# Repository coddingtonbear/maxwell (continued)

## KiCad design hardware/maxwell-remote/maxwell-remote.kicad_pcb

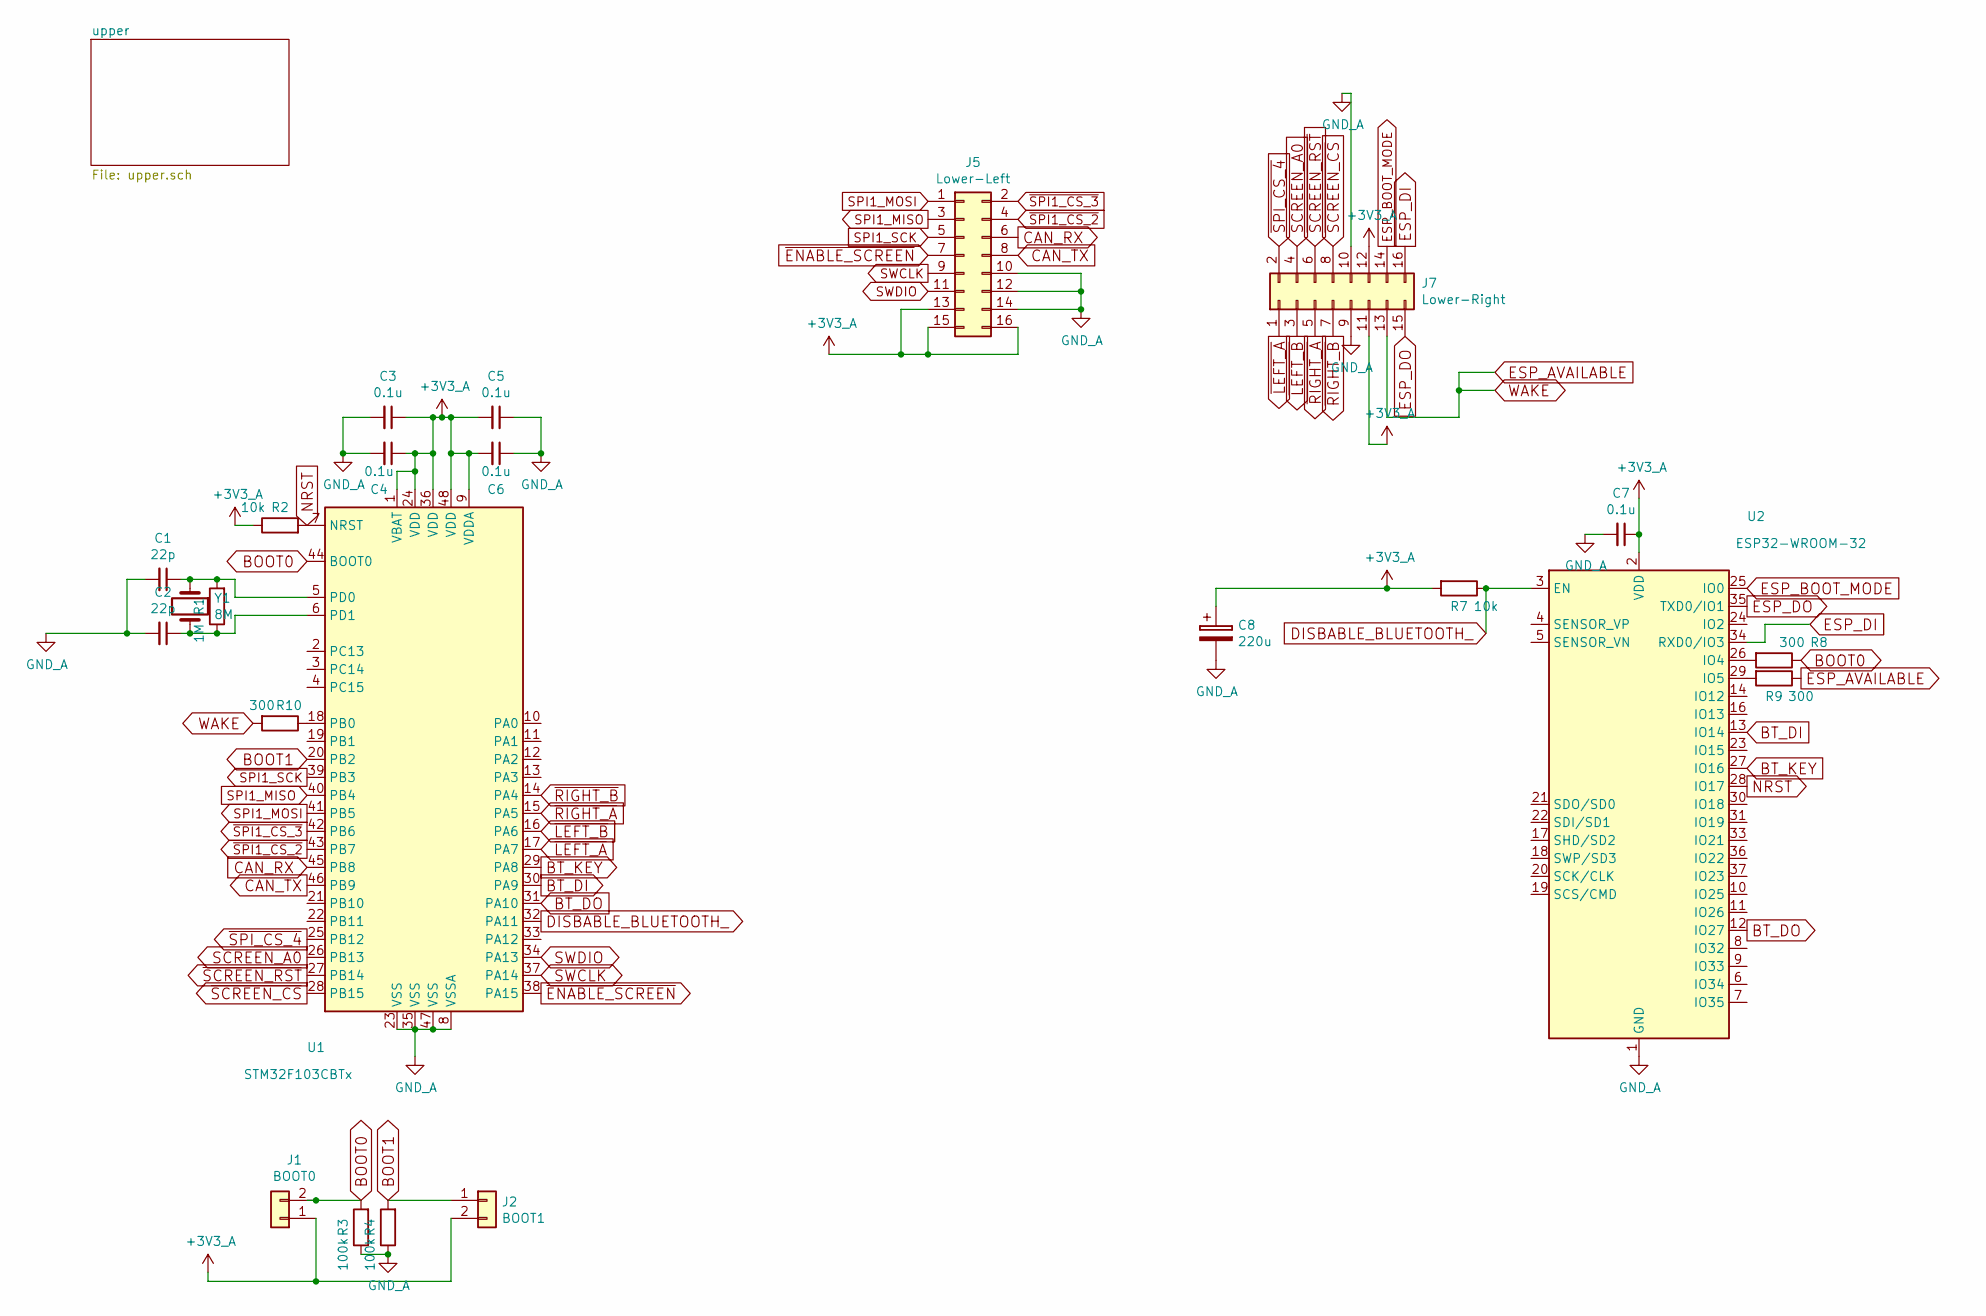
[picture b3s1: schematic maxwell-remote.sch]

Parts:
C1, C2: 22p; 0805_Milling
C3, C4, C5, C6, C7: 0.1u; 0805_Milling
C8: 220u; CP_Tantalum_Case-C_EIA-6032-28_Milling
J1: BOOT0; Pin_Header_Straight_1x02_Pitch1.27mm_JMP
J2: BOOT1; Pin_Header_Straight_1x02_Pitch1.27mm_JMP
J5: Lower-Left; PinHeader_2x08_P2.54mm_Vertical_LargePads
J7: Lower-Right; PinHeader_2x08_P2.54mm_Vertical_LargePads
R1: 1M; 0805_Milling
R2, R7: 10k; 0805_Milling
R3, R4: 100k; 0805_Milling
R8, R9, R10: 300; 0805_Milling
U1: STM32F103CBTx; QFP48-1.27MM-CASTELLATED
U2: ESP32-WROOM-32
Y1: 8M; Abracon-ABM2_LargePads

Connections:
+3V3_A: C3.1, C4.1, C5.2, C6.2, C7.1, C8.1, J1.1, J2.2, J5.13, J5.15, J5.16, J7.11, J7.12, R2.1, R7.2, U1.1 (VBAT), U1.9 (VDDA), U1.24 (VDD), U1.36 (VDD), U1.48 (VDD), U2.2 (VDD)
BOOT0: J1.2, R3.2, R8.1, U1.44 (BOOT0)
BOOT1: J2.1, R4.2, U1.20 (PB2)
BT_DI: U1.30 (PA9), U2.13 (IO14)
BT_DO: U1.31 (PA10), U2.12 (IO27)
BT_KEY: U1.29 (PA8), U2.27 (IO16)
CAN_RX: J5.6, U1.45 (PB8)
CAN_TX: J5.8, U1.46 (PB9)
DISBABLE_BLUETOOTH_: R7.1, U1.32 (PA11), U2.3 (EN)
ESP_AVAILABLE: J7.13, R9.1, R10.2
ESP_BOOT_MODE: J7.14, U2.25 (IO0)
ESP_DI: J7.16, U2.34 (RXD0/IO3)
ESP_DO: J7.15, U2.35 (TXD0/IO1)
GND_A: C1.2, C2.2, C3.2, C4.2, C5.1, C6.1, C7.2, C8.2, J5.10, J5.12, J5.14, J7.9, J7.10, R3.1, R4.1, U1.8 (VSSA), U1.23 (VSS), U1.35 (VSS), U1.47 (VSS), U2.1 (GND), U2.15 (GND), U2.38 (GND)
NRST: R2.2, U1.7 (NRST), U2.28 (IO17)
unnamed: C1.1, R1.2, U1.5 (PD0), Y1.1
unnamed: C2.1, R1.1, U1.6 (PD1), Y1.2
unnamed: R8.2, U2.26 (IO4)
unnamed: R9.2, U2.29 (IO5)
unnamed: R10.1, U1.18 (PB0)
SCREEN_A0: J7.4, U1.26 (PB13)
SPI1_MISO: J5.3, U1.40 (PB4)
SPI1_MOSI: J5.1, U1.41 (PB5)
SPI1_SCK: J5.5, U1.39 (PB3)
SWCLK: J5.9, U1.37 (PA14)
SWDIO: J5.11, U1.34 (PA13)
~ENABLE_SCREEN: J5.7, U1.38 (PA15)
~LEFT_A: J7.1, U1.17 (PA7)
~LEFT_B: J7.3, U1.16 (PA6)
~RIGHT_A: J7.5, U1.15 (PA5)
~RIGHT_B: J7.7, U1.14 (PA4)
~SCREEN_CS: J7.8, U1.28 (PB15)
~SCREEN_RST: J7.6, U1.27 (PB14)
~SPI1_CS_2: J5.4, U1.43 (PB7)
~SPI1_CS_3: J5.2, U1.42 (PB6)
~SPI_CS_4: J7.2, U1.25 (PB12)

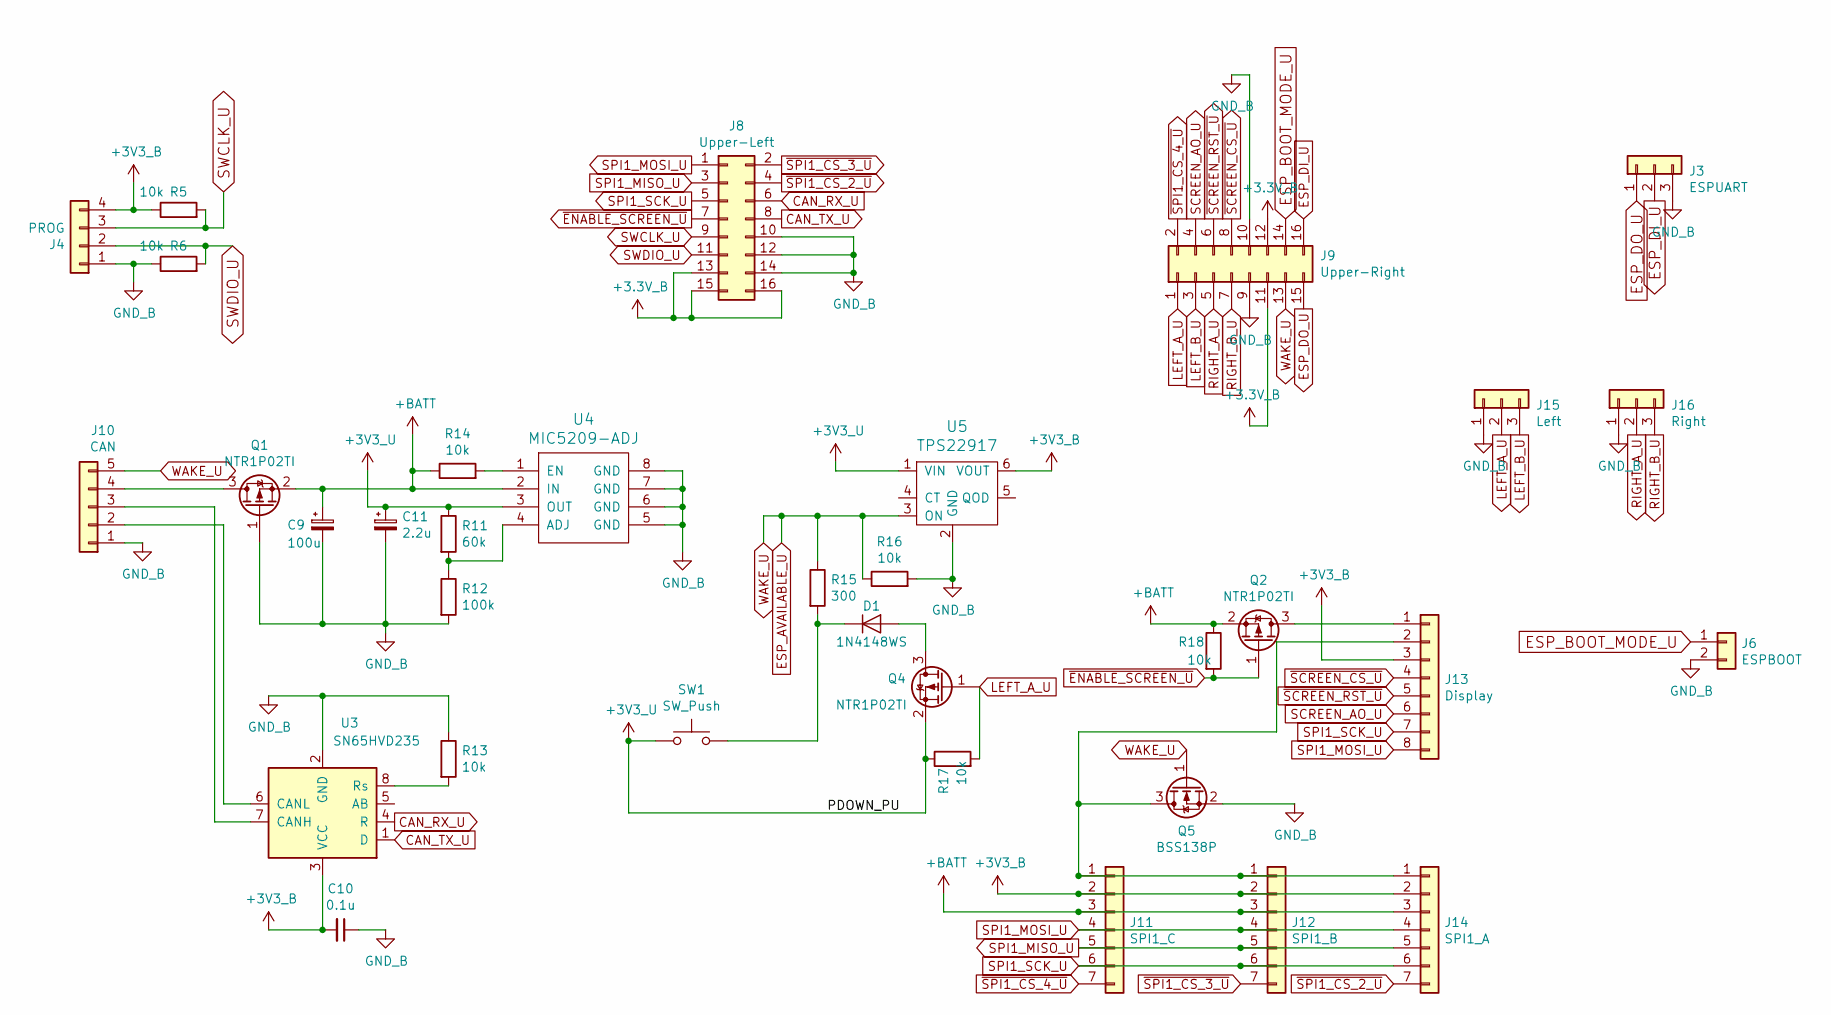
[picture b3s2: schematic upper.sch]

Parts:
C9: 100u; CP_Tantalum_Case-C_EIA-6032-28_Milling
C10: 0.1u; 0805_Milling
C11: 2.2u; CP_Tantalum_Case-C_EIA-6032-28_Milling
D1: 1N4148WS; D_SOD-323_HandSoldering
J3: ESPUART; JST_XH_B03B-XH-A_03x2.50mm_Straight_LargePads
J4: PROG; Pin_Header_Straight_1x04_Pitch2.54mm_LargePads
J6: ESPBOOT; Pin_Header_Straight_1x02_Pitch1.27mm_JMP
J8: Upper-Left; PinHeader_2x08_P2.54mm_Vertical_LargePads
J9: Upper-Right; PinHeader_2x08_P2.54mm_Vertical_LargePads
J10: CAN; JST_XH_B05B-XH-A_05x2.50mm_Straight_LargePads
J11: SPI1_C; JST_XH_B07B-XH-A_07x2.50mm_Straight_LargePads
J12: SPI1_B; JST_XH_B07B-XH-A_07x2.50mm_Straight_LargePads
J13: Display; JST_XH_B08B-XH-A_08x2.50mm_Straight_LargePads
J14: SPI1_A; JST_XH_B07B-XH-A_07x2.50mm_Straight_LargePads
J15: Left; JST_XH_B03B-XH-A_03x2.50mm_Straight_LargePads
J16: Right; JST_XH_B03B-XH-A_03x2.50mm_Straight_LargePads
Q1, Q2, Q4: NTR1P02TI; SOT-23_LargePads
Q5: BSS138P; SOT-23_LargePads
R5, R6, R13, R14, R16, R17, R18: 10k; 0805_Milling
R11: 60k; 0805_Milling
R12: 100k; 0805_Milling
R15: 300; 0805_Milling
SW1: SW_Push; SMD_MINI_BLACK_TACTILE_SWITCH
U3: SN65HVD235; SOIC-8_3.9x4.9mm_P1.27mm
U4: MIC5209-ADJ; SOIC-8_3.9x4.9mm_P1.27mm_LargePads
U5: TPS22917; SOT-23-6_Handsoldering

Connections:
+3V3_U: C11.1, Q4.2 (S), R11.1, R17.1, SW1.1, U4.3 (OUT), U5.1 (VIN)
+BATT: C9.1, J11.3, J12.3, J14.3, Q1.2 (S), Q2.2 (S), R14.1, R18.1, U4.2 (IN)
CAN_RX_U: J8.6, U3.4 (R)
CAN_TX_U: J8.8, U3.1 (D)
ESP_AVAILABLE_U: J9.13, J10.5, Q5.1 (G), R15.1, R16.1, U5.3 (ON)
ESP_BOOT_MODE_U: J6.1, J9.14
ESP_DI_U: J3.2, J9.16
ESP_DO_U: J3.1, J9.15
GND_B: C9.2, C10.1, C11.2, J3.3, J4.1, J6.2, J8.10, J8.12, J8.14, J9.9, J9.10, J10.1, J15.1, J16.1, Q1.1 (G), Q5.2 (S), R6.1, R12.2, R13.1, R16.2, U3.2 (GND), U4.5 (GND), U4.6 (GND), U4.7 (GND), U4.8 (GND), U5.2 (GND)
LEFT_A_U: J9.1, J15.2, Q4.1 (G), R17.2
LEFT_B_U: J9.3, J15.3
unnamed: D1.1 (K), R15.2, SW1.2
unnamed: D1.2 (A), Q4.3 (D)
unnamed: J10.2, U3.6 (CANL)
unnamed: J10.3, U3.7 (CANH)
unnamed: J10.4, Q1.3 (D)
unnamed: J11.1, J12.1, J13.2, J14.1, Q5.3 (D)
unnamed: J13.1, Q2.3 (D)
unnamed: R11.2, R12.1, U4.4 (ADJ)
unnamed: R13.2, U3.8 (Rs)
unnamed: R14.2, U4.1 (EN)
RIGHT_A_U: J9.5, J16.2
RIGHT_B_U: J9.7, J16.3
SCREEN_AO_U: J9.4, J13.6
SPI1_MISO_U: J8.3, J11.5, J12.5, J14.5
SPI1_MOSI_U: J8.1, J11.4, J12.4, J13.8, J14.4
SPI1_SCK_U: J8.5, J11.6, J12.6, J13.7, J14.6
SWCLK_U: J4.3, J8.9, R5.2
SWDIO_U: J4.2, J8.11, R6.2
~ENABLE_SCREEN_U: J8.7, Q2.1 (G), R18.2
~SCREEN_CS_U: J9.8, J13.4
~SCREEN_RST_U: J9.6, J13.5
~SPI1_CS_2_U: J8.4, J14.7
~SPI1_CS_3_U: J8.2, J12.7
~SPI1_CS_4_U: J9.2, J11.7

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
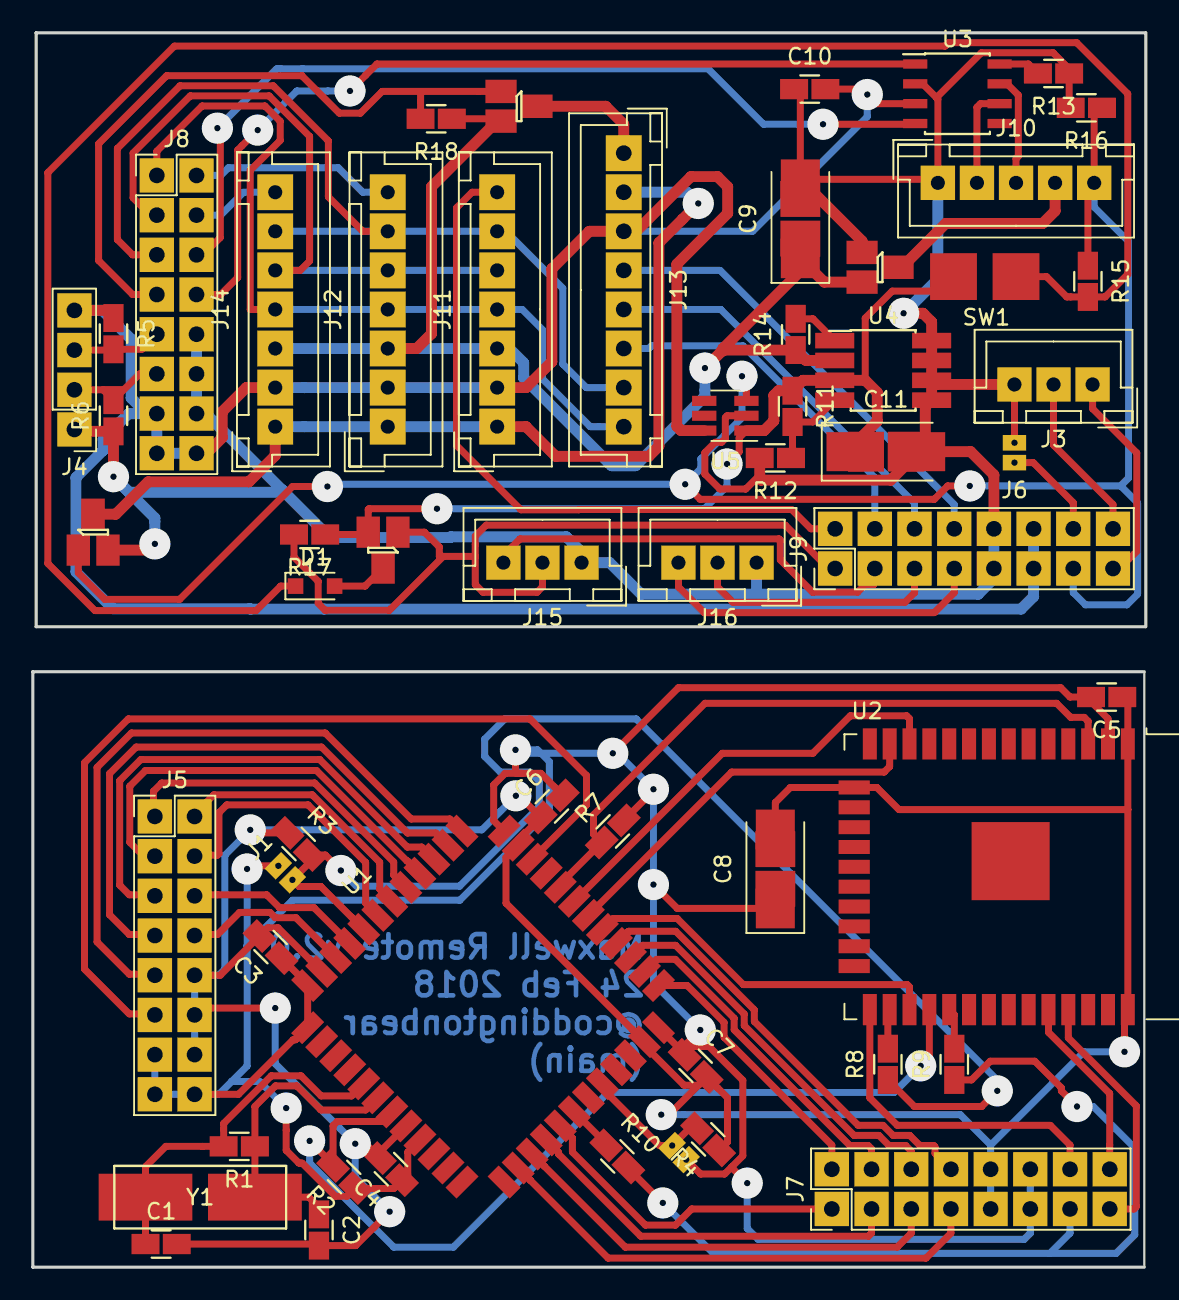
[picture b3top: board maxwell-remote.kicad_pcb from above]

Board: 2 copper layers, 71.2 x 79.0 mm, 57 parts (1 on the bottom side), 72 nets.

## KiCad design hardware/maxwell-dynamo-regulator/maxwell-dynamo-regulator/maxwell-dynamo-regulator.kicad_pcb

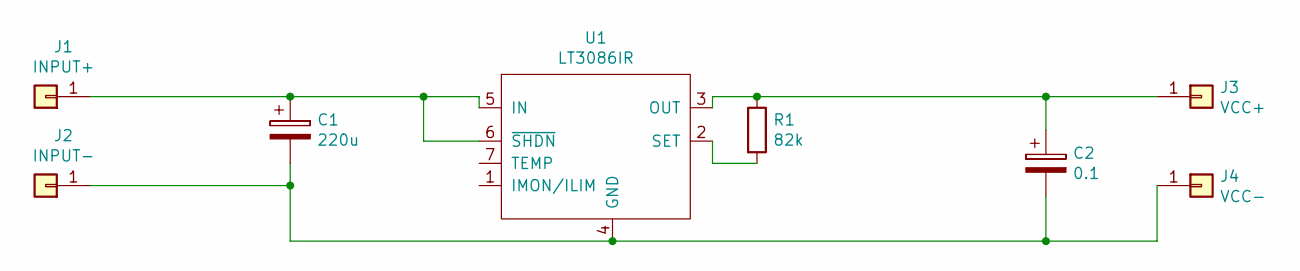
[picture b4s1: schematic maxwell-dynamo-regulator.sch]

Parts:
C1: 220u; C_Elec_8x10.2
C2: 0.1; JST_XH_B02B-XH-A_02x2.50mm_Straight_LargePads
J1: INPUT+; PinHeader_1x01_P2.54mm_Vertical
J2: INPUT-; PinHeader_1x01_P2.54mm_Vertical
J3: VCC+; PinHeader_1x01_P2.54mm_Vertical
J4: VCC-; PinHeader_1x01_P2.54mm_Vertical
R1: 82k; 0805_Milling
U1: LT3086IR; TO-263-7_TabPin4

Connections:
unnamed: C1.1, J1.1, U1.5 (IN), U1.6 (~SHDN)
unnamed: C1.2, C2.2, J2.1, J4.1, U1.4 (GND)
unnamed: C2.1, J3.1, R1.1, U1.3 (OUT)
unnamed: R1.2, U1.2 (SET)

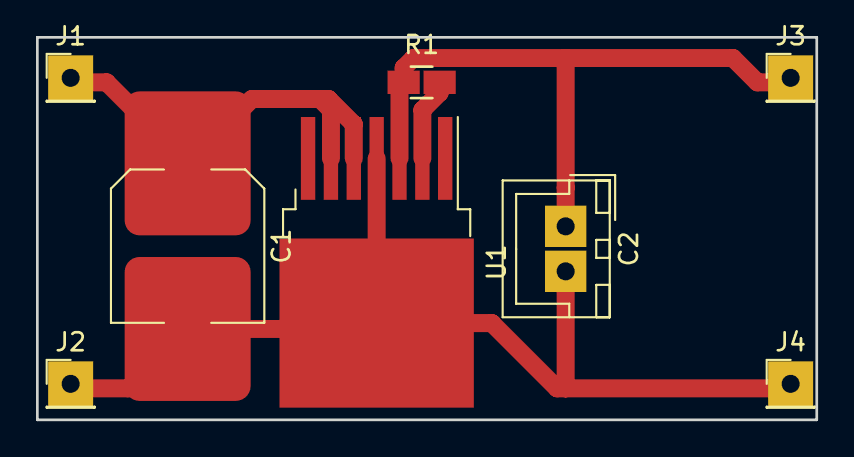
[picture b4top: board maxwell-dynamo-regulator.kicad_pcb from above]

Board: 2 copper layers, 43.3 x 21.2 mm, 8 parts (0 on the bottom side), 4 nets.

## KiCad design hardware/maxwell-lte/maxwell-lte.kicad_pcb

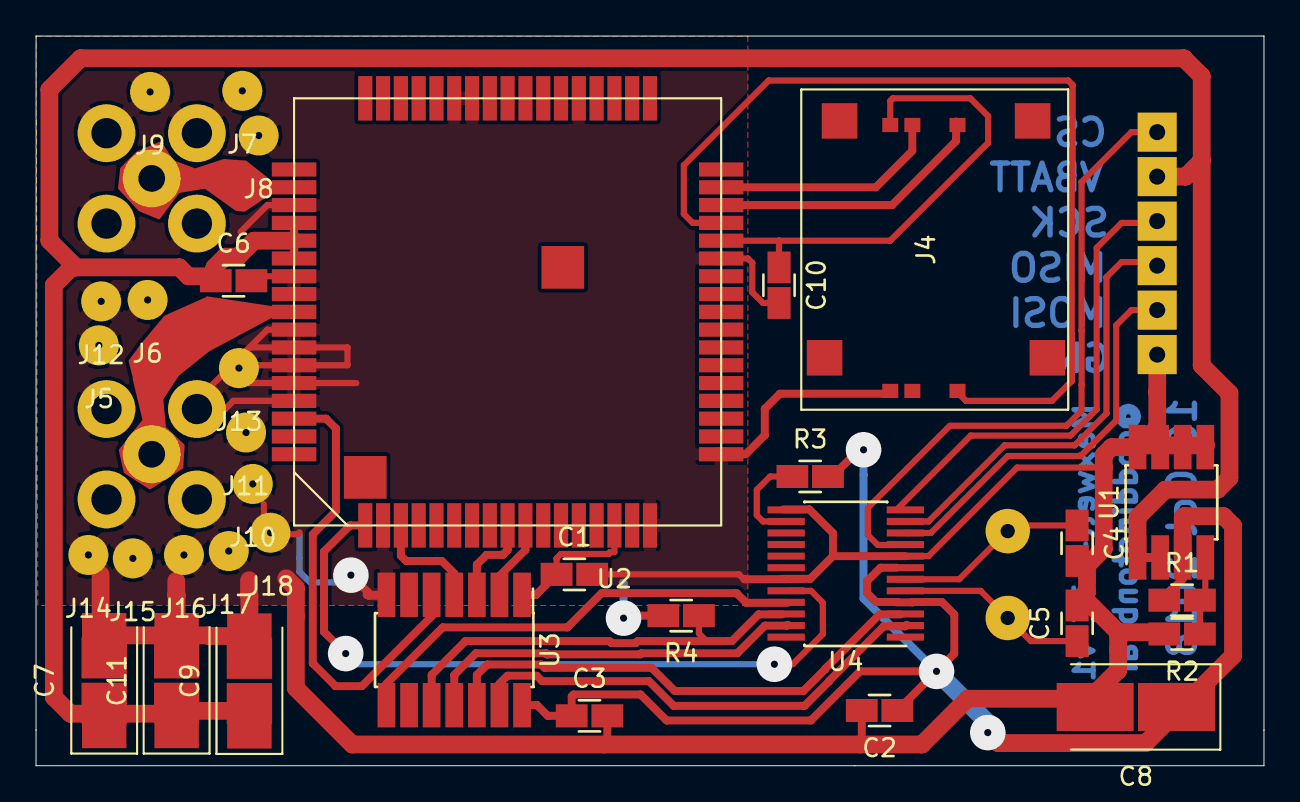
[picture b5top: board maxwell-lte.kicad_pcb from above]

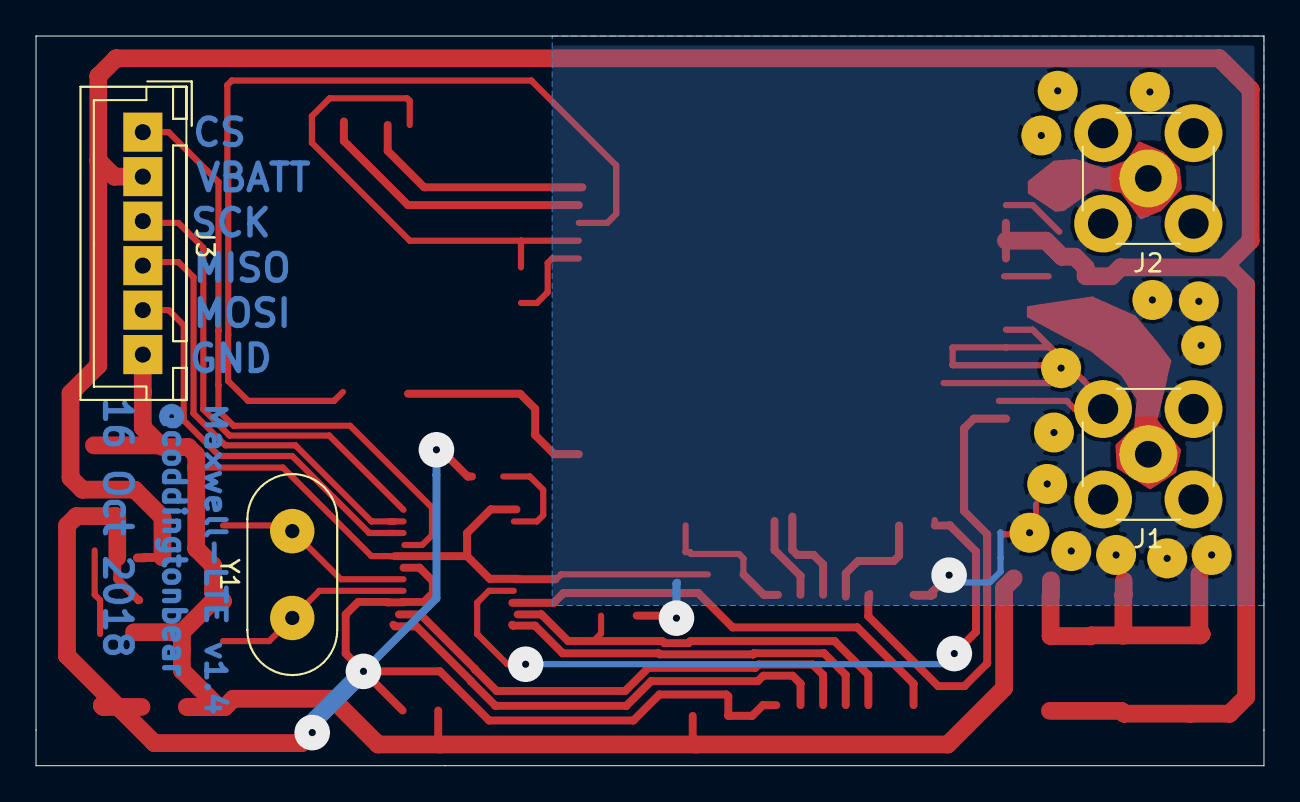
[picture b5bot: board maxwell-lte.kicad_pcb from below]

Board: 2 copper layers, 69.0 x 41.0 mm, 38 parts (4 on the bottom side), 28 nets.

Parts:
C1, C2, C3, C6, C10: 0.1u; 0805_Milling
C4, C5: 22p; 0805_Milling
C7, C9, C11: 220u / TAJC227K006RNJ; CP_Tantalum_Case-C_EIA-6032-28_Milling
C8: 100u / NTC-T107K10TRDF; CP_Tantalum_Case-D_EIA-7343-31_Milling
J1: LTE; SMA_Amphenol_132134_Vertical_Largepads
J2: GPS; SMA_Amphenol_132134_Vertical_Largepads
J3: Input; JST_XH_B06B-XH-A_06x2.50mm_Straight_LargePads
J4: SIM_Card; 78800-0001
J5, J6, J7, J8, J9, J10, J11, J12, J13, J15, J16, J17, J18: Stitching; Thermal_Relief_Via_Milling
J14: Stiching; Thermal_Relief_Via_Milling
R1: R1; 0805_Milling
R2: R2; 0805_Milling
R3: 1k; 0805_Milling
R4: 10k; 0805_Milling
U1: MIC5209-ADJ; SOIC-8_3.9x4.9mm_P1.27mm_LargePads
U2: SIM7000A; SIM7000
U3: TXB0104D; SOIC-14_3.9x8.7mm_P1.27mm_LargePads
U4: SC16IS750IPW; TSSOP-24_4.4x7.8mm_P0.65mm_LargePads
Y1: Crystal; Crystal_HC49-U_Vertical_LargePads

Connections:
+1V8: C1.1, U2.15, U3.1
+3V3: C2.1, C3.1, C8.1, R1.1, R3.2, U1.3, U3.14, U4.4, U4.7
+BATT: C6.1, C7.1, C9.1, C11.1, J3.2, U1.1, U1.2, U2.55, U2.56, U2.57
/GPS_ANT: J2.1, U2.53
/LTE_ANT: J1.1, U2.60
/LTE_DI_H: U3.13, U4.2
/LTE_DI_L: U2.10, U3.2
/LTE_DO_H: U3.12, U4.3
/LTE_DO_L: U2.9, U3.3
/LTE_DTR_H: U3.11, U4.23
/LTE_DTR_L: U2.3, U3.4
/STATUS_H: R4.1, U3.10, U4.22
CS: J3.1, U4.9
EN_OUTPUT: U3.8, U4.21
GND: C1.2, C2.2, C3.2, C4.2, C5.2, C6.2, C7.2, C8.2, C9.2, C10.2, C11.2, J1.2, J2.2, J3.6, J4.5, J5.1, J6.1, J7.1, J8.1, J9.1, J10.1, J11.1, J12.1, J13.1, J14.1, J15.1, J16.1, J17.1, J18.1, R2.2, R4.2, U1.5, U1.6, U1.7, U1.8, U2.2, U2.17, U2.18, U2.29, U2.39, U2.45, U2.46, U2.54, U2.58, U2.59, U2.61, U2.62, U2.63, U2.64, U2.65, U3.7, U4.8, U4.13, U4.19
MISO: J3.4, U4.11
MOSI: J3.5, U4.10
unnamed: C4.1, U4.6, Y1.2
unnamed: C5.1, U4.5, Y1.1
unnamed: C10.1, J4.1, U2.30
unnamed: J4.2, U2.33
unnamed: J4.3, U2.32
unnamed: J4.7, U2.31
unnamed: R1.2, R2.1, U1.4
unnamed: R3.1, U4.14
PWRKEY: U2.1, U4.20
SCK: J3.3, U4.12
STATUS: U2.66, U3.5

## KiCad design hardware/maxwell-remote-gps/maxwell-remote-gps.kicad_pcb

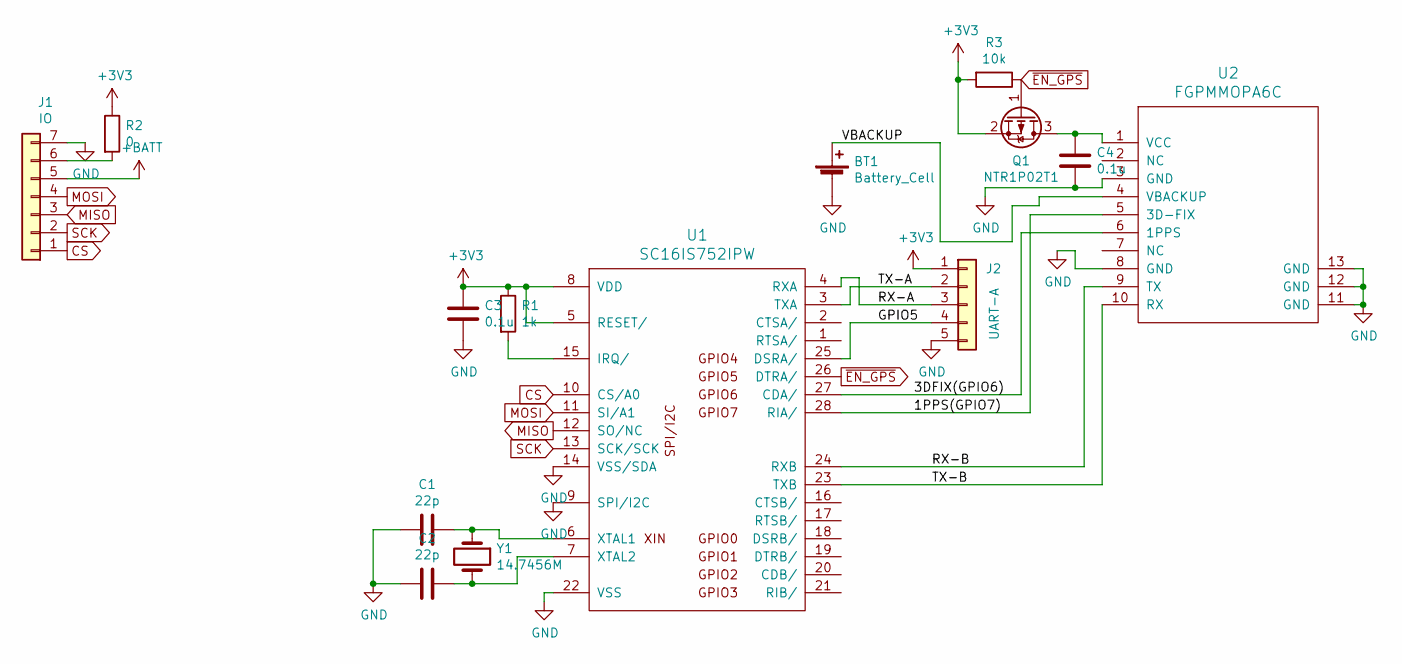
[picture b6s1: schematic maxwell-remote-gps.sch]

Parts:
BT1: Battery_Cell; JST_EH_B02B-EH-A_02x2.50mm_Straight_LargePads
C1, C2: 22p; 0805_Milling
C3, C4: 0.1u; 0805_Milling
J1: IO; JST_XH_B07B-XH-A_07x2.50mm_Straight_LargePads
J2: UART-A; JST_EH_B05B-EH-A_05x2.50mm_Straight_LargePads
Q1: NTR1P02T1; SOT-23_LargePads
R1: 1k; 0805_Milling
R2: 0; 0805_Milling
R3: 10k; 0805_Milling
U1: SC16IS752IPW; TSSOP-28_4.4x9.7mm_P0.65mm
U2: FGPMMOPA6C
Y1: 14.7456M; Crystal_HC49-U_Vertical_LargePads

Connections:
+3V3: C3.1, J2.1, Q1.2 (S), R1.1, R2.1, R3.2, U1.5 (RESET/), U1.8 (VDD)
/1PPS(GPIO7): U1.28 (RIA/), U2.5 (3D-FIX)
/3DFIX(GPIO6): U1.27 (CDA/), U2.6 (1PPS)
/GPIO5: J2.4, U1.25 (DSRA/)
/RX-A: J2.3, U1.4 (RXA)
/RX-B: U1.24 (RXB), U2.9 (TX)
/TX-A: J2.2, U1.3 (TXA)
/TX-B: U1.23 (TXB), U2.10 (RX)
/VBACKUP: BT1.1 (+), U2.4 (VBACKUP)
CS: J1.1, U1.10 (CS/A0)
GND: BT1.2 (-), C1.2, C2.2, C3.2, C4.2, J1.7, J2.5, U1.9 (SPI/I2C), U1.14 (VSS/SDA), U1.22 (VSS), U2.3 (GND), U2.8 (GND), U2.11 (GND), U2.12 (GND), U2.13 (GND)
MISO: J1.3, U1.12 (SO/NC)
MOSI: J1.4, U1.11 (SI/A1)
unnamed: C1.1, U1.6 (XTAL1), Y1.1
unnamed: C2.1, U1.7 (XTAL2), Y1.2
unnamed: C4.1, Q1.3 (D), U2.1 (VCC)
unnamed: J1.6, R2.2
unnamed: R1.2, U1.15 (IRQ/)
SCK: J1.2, U1.13 (SCK/SCK)
~EN_GPS: Q1.1 (G), R3.1, U1.26 (DTRA/)

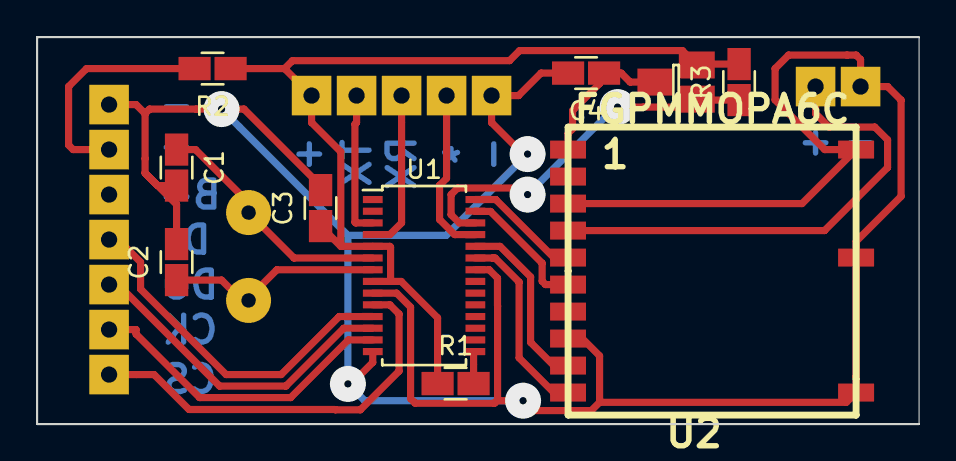
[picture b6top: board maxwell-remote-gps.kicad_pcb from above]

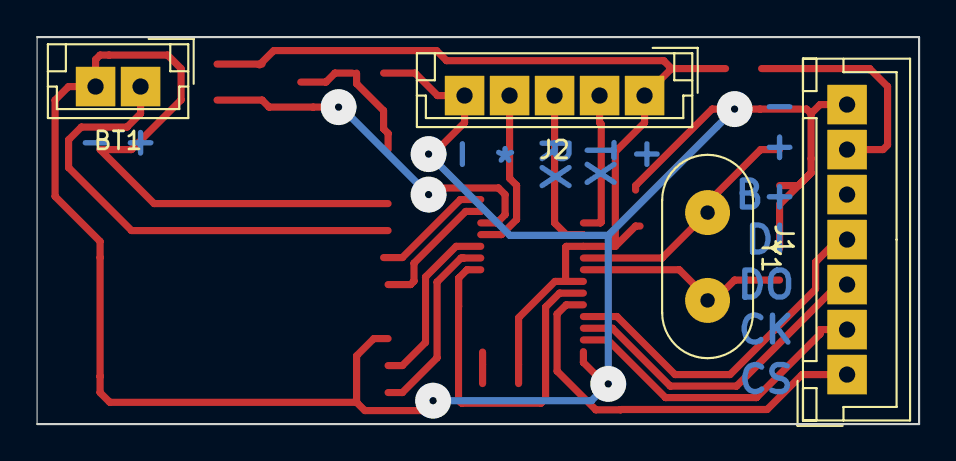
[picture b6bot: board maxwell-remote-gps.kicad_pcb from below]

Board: 2 copper layers, 49.0 x 21.5 mm, 14 parts (4 on the bottom side), 20 nets.

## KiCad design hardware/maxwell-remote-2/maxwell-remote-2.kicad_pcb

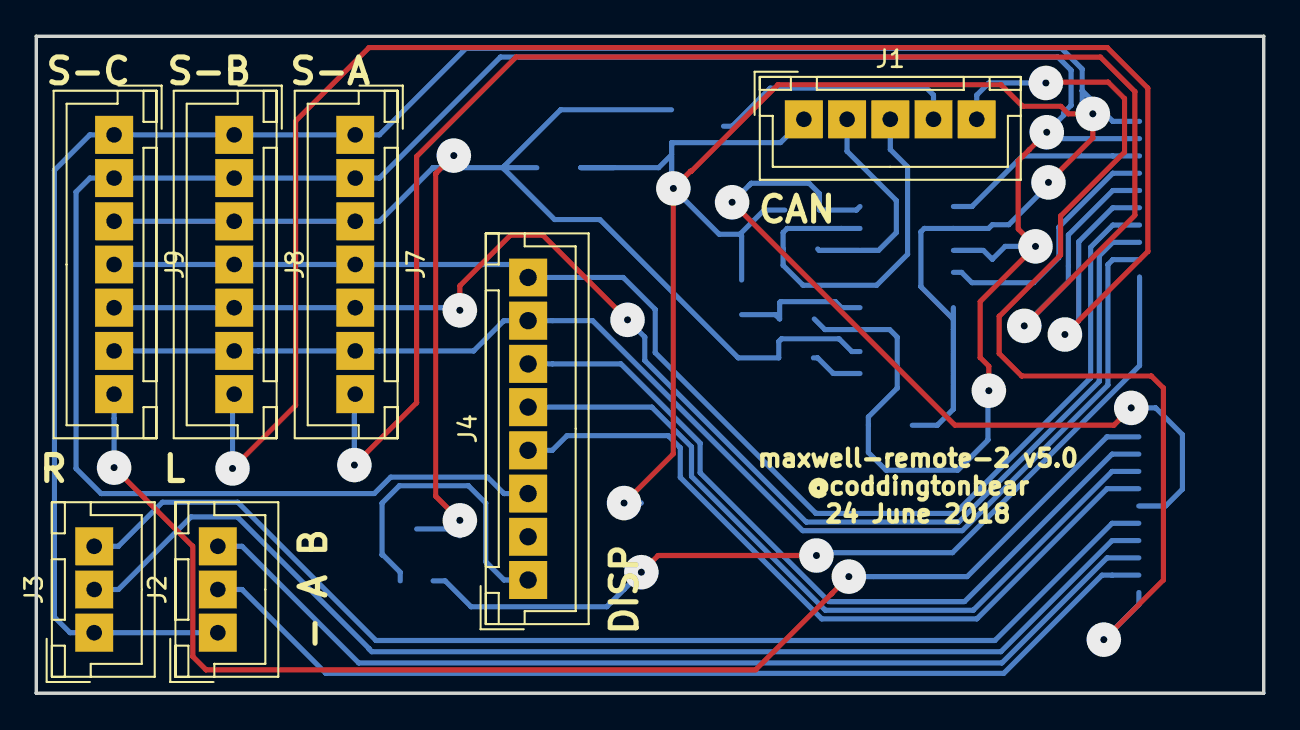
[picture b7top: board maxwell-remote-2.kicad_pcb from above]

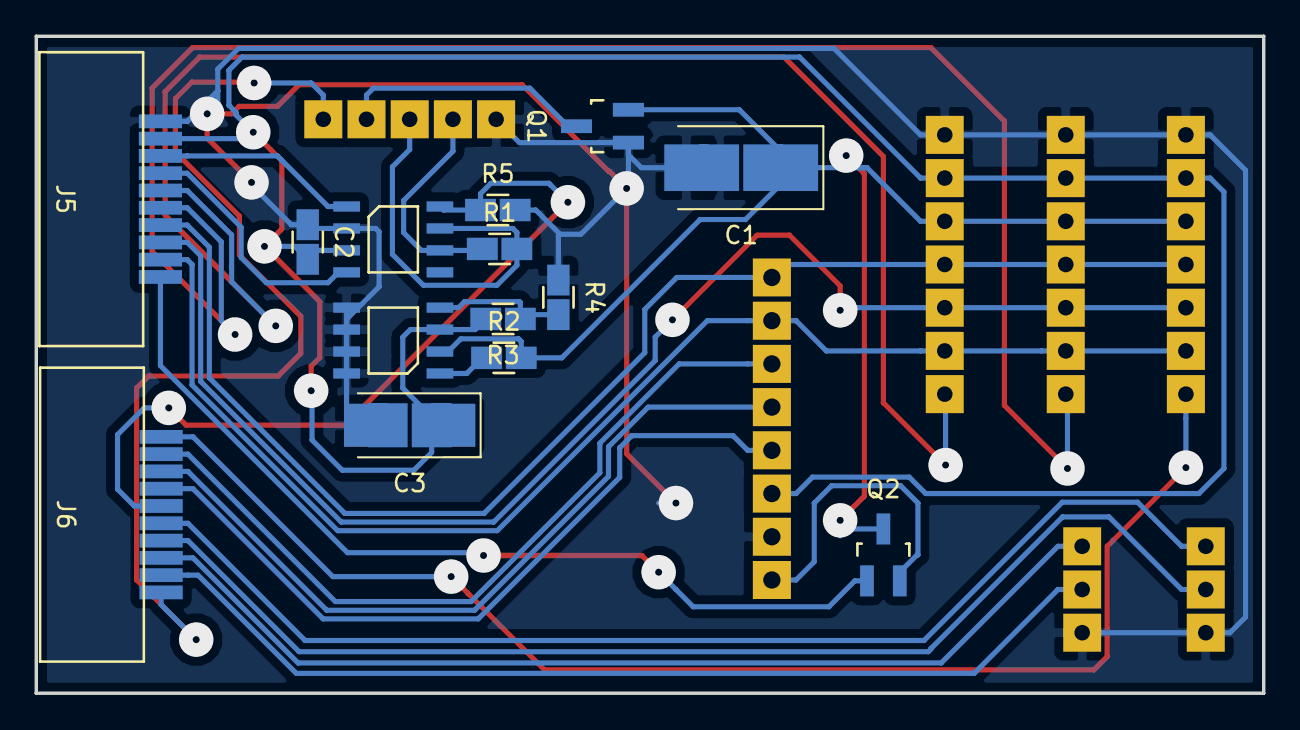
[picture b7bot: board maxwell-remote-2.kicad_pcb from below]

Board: 2 copper layers, 71.0 x 38.0 mm, 21 parts (14 on the bottom side), 27 nets.

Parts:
C1: 100u; CP_Tantalum_Case-D_EIA-7343-31_Milling
C2: 0.1u; 0805_Milling
C3: 2.2u; CP_Tantalum_Case-C_EIA-6032-28_Milling
J1: INPUT; JST_XH_B05B-XH-A_05x2.50mm_Straight_LargePads
J2: Left; JST_XH_B03B-XH-A_03x2.50mm_Straight_LargePads
J3: Right; JST_XH_B03B-XH-A_03x2.50mm_Straight_LargePads
J4: DISPLAY; JST_XH_B08B-XH-A_08x2.50mm_Straight_LargePads
J5: FPC-1; 10P_FPC_1.0mm
J6: FPC-2; 10P_FPC_1.0mm
J7: SPI1_A; JST_XH_B07B-XH-A_07x2.50mm_Straight_LargePads
J8: SPI1_B; JST_XH_B07B-XH-A_07x2.50mm_Straight_LargePads
J9: SPI1_C; JST_XH_B07B-XH-A_07x2.50mm_Straight_LargePads
Q1, Q2: NDS332P; SOT-23_Handsoldering
R1: 120; 0805_Milling
R2, R5: 10k; 0805_Milling
R3: 60k; 0805_Milling
R4: 100k; 0805_Milling
U1: SN65HVD235; SOIC-8
U2: MIC5209-ADJ; SOIC-8

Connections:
+3V3: C2.2, C3.1, J4.3, J5.9, J7.2, J8.2, J9.2, R3.2, U1.3, U2.3
+BATT: C1.1, J7.3, J8.3, J9.3, Q1.2, Q2.3, R2.2, U2.2
CAN+: J1.3, R1.2, U1.7
CAN-: J1.2, R1.1, U1.6
CAN_RX: J5.7, U1.4
CAN_TX: J5.8, U1.1
ENABLE_SCREEN: J5.1, Q2.1
GND: C1.2, C2.1, C3.2, J1.1, J2.1, J3.1, J4.2, J5.10, J7.1, J8.1, J9.1, Q1.1, R4.1, R5.2, U1.2, U2.5, U2.6, U2.7, U2.8
unnamed: J1.4, Q1.3
unnamed: J4.1, Q2.2
unnamed: R2.1, U2.1
unnamed: R3.1, R4.2, U2.4
SCREEN_A0: J4.6, J6.9
SPI1_MISO: J5.3, J7.5, J8.5, J9.5
SPI1_MOSI: J4.8, J5.4, J7.4, J8.4, J9.4
SPI1_SCK: J4.7, J5.2, J7.6, J8.6, J9.6
WAKE: J1.5, J6.1
~ENABLE_CAN: J6.6, R5.1, U1.8
~LEFT_A: J2.2, J6.2
~LEFT_B: J2.3, J6.3
~RIGHT_A: J3.2, J6.4
~RIGHT_B: J3.3, J6.5
~SCREEN_CS: J4.4, J6.7
~SCREEN_RST: J4.5, J6.8
~SPI1_CS_2: J5.6, J7.7
~SPI1_CS_3: J5.5, J8.7
~SPI_CS_4: J6.10, J9.7

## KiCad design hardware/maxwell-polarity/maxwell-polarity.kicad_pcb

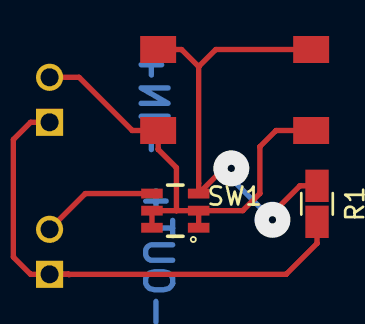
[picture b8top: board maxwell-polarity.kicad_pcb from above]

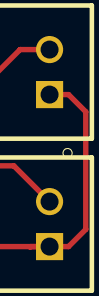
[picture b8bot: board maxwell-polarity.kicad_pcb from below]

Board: 2 copper layers, 5 parts (2 on the bottom side), 4 nets.

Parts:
J1: Output; JST_XHP-2
J2: Battery; JST_XHP-2
R1: 100k; 0805_Milling
SW1: SW_Push; SMD_RED_TACTILE_SWITCH
U1: STT3P2UH7; SOT23-6

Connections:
GND: J1.1, J2.1, R1.2
unnamed: J1.2, U1.4
unnamed: J2.2, SW1.2, U1.1, U1.2, U1.5, U1.6
unnamed: R1.1, SW1.1, U1.3

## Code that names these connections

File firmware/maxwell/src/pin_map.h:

#pragma once

#include <PCA9536.h>

#define PIN_BT_DISABLE_ PC7
#define PIN_BT_KEY PC6

#define PIN_SPI_CS_A PA2
#define PIN_SPI_CS_B PA1

#define PIN_NEOPIXEL PA7
#define PIN_ENABLE_NEOPIXEL PC4
#define PIN_ENABLE_AUX PB10

#define DISPLAY_BACKLIGHT_ON_ PB1
#define DISPLAY_CS PA0
#define DISPLAY_DC PC5
#define DISPLAY_RST PB0

#define PIN_POWER_ON PB3

#define BUTTON_LEFT_A PC13
#define BUTTON_LEFT_B PC14
#define BUTTON_RIGHT_A PC15
#define BUTTON_RIGHT_B PC3

// EXTERNAL: LTE Module
#define PIN_LTE_DTR 7
#define PIN_LTE_STATUS 6
#define PIN_LTE_OE 5
#define PIN_LTE_PWRKEY 4

// EXTERNAL: Power/ADC
#define PIN_ADC_BATT_VOLTAGE 1
#define PIN_ADC_DYNAMO_VOLTAGE 2

// EXTERNAL: Power/IO
#define PIN_RECTIFIER_RELAY_A IO0
#define PIN_RECTIFIER_RELAY_B IO1
#define PIN_PWR_I_BATT_CHARGING IO2

#define BTSerial Serial
#define UART2 Serial1
#define UART3 Serial2
#define UART4 Serial3
#define UART5 Serial4

#define I2C_SCL PB6
#define I2C_SDA PB7

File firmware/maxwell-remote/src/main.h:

#pragma once

#include <Arduino.h>
#include <RTClock.h>
#include <SC16IS750.h>

#define UTC_OFFSET -7

#define DISPLAY_REFRESH_INTERVAL 100
#define GPS_REFRESH_INTERVAL 1720
#define TIMESTAMP_REFRESH_INTERVAL 9000

#define LONG_PRESS_TIMEOUT 2000
#define LONG_PRESS_INTERVAL 500

#define BT_DISABLE_ PA11
#define BT_KEY PA8

#define WAKE PB0

#define RIGHT_A PA5
#define RIGHT_B PA4
#define LEFT_B PA6
#define LEFT_A PA7

#define SPI_CS2 PB7
#define SPI_CS3 PB6
#define SPI_CS4 PB12

void setup();
void loop();
void enableCanDebug(bool);
void sleep();

void taskUpdateDisplayCallback();
void taskGpsRefreshCallback();
void taskTimestampRefreshCallback();

extern RTClock Clock;
extern SC16IS750 GPSUart;
extern SC16IS750 AlternateUart;

#define Output Serial

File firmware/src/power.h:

#include <Arduino.h>

#define POWER_ON PB0
#define ENABLE_AUX_DEVICES PB9
#define ENABLE_BATT_CHARGE_ PB14
#define I_BATTERY_CHARGING_ PA3
#define I_DYNAMO_VOLTAGE PB1
#define I_BATTERY_VOLTAGE PC5
#define I_CURRENT_SENSE PC4

// USB Charging
#define USB_ENABLE_ PA2

#define VOLTAGE_DYNAMO 1
#define VOLTAGE_BATTERY 2
#define VOLTAGE_SENSE 3

#define SENSE_RESISTOR_VALUE 0.02

int getRawVoltageAdcValue(uint source);
double getVoltage(uint source);
double getCurrentUsage();
void enableBatteryCharging(bool);
void enableAuxDevices(bool);

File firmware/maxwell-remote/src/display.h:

#pragma once

#include <Arduino.h>
#include "U8g2lib.h"
#include "menu.h"

#define BACKLIGHT_ON_ PA15
#define DISPLAY_CS PB15
#define DISPLAY_DC PB13
#define DISPLAY_RST PB14

#define SMALL_DISPLAY_FONT u8g2_font_helvB12_tr
#define SMALL_DISPLAY_FONT_HEIGHT 12
#define LARGE_DISPLAY_FONT u8g2_font_helvB24_tr
#define LARGE_DISPLAY_FONT_HEIGHT 24

#define DISPLAY_WIDTH 128
#define DISPLAY_HEIGHT 64

#define MENU_EXEC_NOTICE_TIMEOUT 100
#define MENU_TIMEOUT 5000

#define FONT_HEIGHT 14

#define STATUS_PHASE_DURATION 600
#define ALERT_DURATION 10000;

class DisplayManager {
    public:
        DisplayManager(MenuList*);

        void begin();
        void enable(bool _enabled=true);
        void refresh();
        void sleep();

        void setContrast(uint8_t);
        void setAutosleep(bool _enabled=true);
        void addAlert(String message);
        void redisplayAlert();

        void enableBacklight(bool _enabled=true);
        void toggleBacklight();

        void menuKeepalive();
        void up();
        void down();
        void in();
        void out();

        void enableTimeout(bool);
        void setActionTimeout();

    protected:
        void wake();

        MenuList* getCurrentMenu();

        char currentAlert[255];
        uint32_t currentAlertEnd = 0;

        bool enabled = true;
        bool autosleep = false;
        bool sleeping = false;
        bool backlightOn = false;
        bool timeout = true;

        uint8_t menuDepth = 0;
        uint8_t menuPosition[10];

        void showMenu();
        void executeMenuCommand(void(*)());

        uint8_t statusPhase = 0;
        uint8_t statusPhaseCount = 10;
        unsigned long statusPhaseEnds = 0;

        unsigned long showMenuUntil = 0;
        unsigned long showMenuExecNoticeUntil = 0;

        MenuList* mainMenu;
};

extern DisplayManager Display;
